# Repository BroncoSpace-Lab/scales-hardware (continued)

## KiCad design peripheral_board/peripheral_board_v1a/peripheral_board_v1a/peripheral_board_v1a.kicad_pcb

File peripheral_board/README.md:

# Peripheral Board
The peripheral board is conprized for two different purposes.

1. Inter communication between the Jetson and i.MX8X.
2. Gives the end user access to ports to attach the peripherals that they want. 
    The ports given to user:
    * At least 1 Ethernet port
    * At least 2 SPI/UART ports
## General Information of each major block of the board

The above image is of the root page of the schematic with basic infomration and a block diagram of the board and its use.

This is the front of the board in KiCad's 3D view.

Some of the models are not in the correct placement beacuse their 3D model was incorrectly created. They are placed in the correctly on the board.

This is the back of the board in KiCad's 3D view.

## Break down of the three core parts
Each section is about the individual chips and it has basic information on the layout.

### Raspberry Pi
[JLC Link](https://jlcpcb.com/partdetail/RaspberryPi-RP2350A/C42411118) to the RP2350A.

Layout and other information from the [PROVES dev kit](https://github.com/proveskit) and the [Raspberry Pi Hardware minimum configuration](extension://efaidnbmnnnibpcajpcglclefindmkaj/https://datasheets.raspberrypi.com/rp2350/hardware-design-with-rp2350.pdf)

This can be bought as a development board as a standalone product for project use.

### Wiznet
[JLC Link](https://jlcpcb.com/partdetail/Wiznet-W5500/C32843) to the Wiznet W5500.

Layout and other informatuon from the [PROVES dev kit](https://github.com/proveskit) and [Wiznet W5500 Eval Board](https://github.com/Wiznet/W5500-EVB)

This product can be purchased bought as [WIZ850io](https://wiznet.io/products/network-modules/wiz850io) which is a compact module of just the chip and an RJ45 or as [W5500-EVB-Pico](https://wiznet.io/products/evaluation-boards/w5500-evb-pico) which is the chip with a Raspberry Pi Pico with open holes for GPIO manipulation.

There is [Coding with CircuitPython on W5100S-EVB-Pico2](https://maker.wiznet.io/viktor/projects/coding-with-circuitpython-on-w5100s-evb-pico2/) that is on the Wiznet Makers website that should be easy to follow for setting up the Wiznet RP combination.

### 5-port Ethernet Switch
[JLC Link](https://jlcpcb.com/partdetail/MicrochipTech-KSZ8795CLXIC/C69416) to the Microchip 5-Port Ethernet Switch.

The original eval board is no longer made but there is an update of the chip with a [newer Eval Board](https://www.microchip.com/en-us/development-tool/KSZ8795CLXD-EVAL). For this project we will be using the strap in mode of the chip to be just a 4 port etherenet switch that will not require any software or modification. The last port will be left open for possible future iterations.

## How to used the board
*Still in Development*

*Taken with a grain of salt*
The Wizenet W5500 and Microchip KSZ8795CLXIC should be preconfigured to work as is. The Microchip KSZ8795CLXIC could be one reconfigured to utilize the 5th port as different data rates if they are needed.

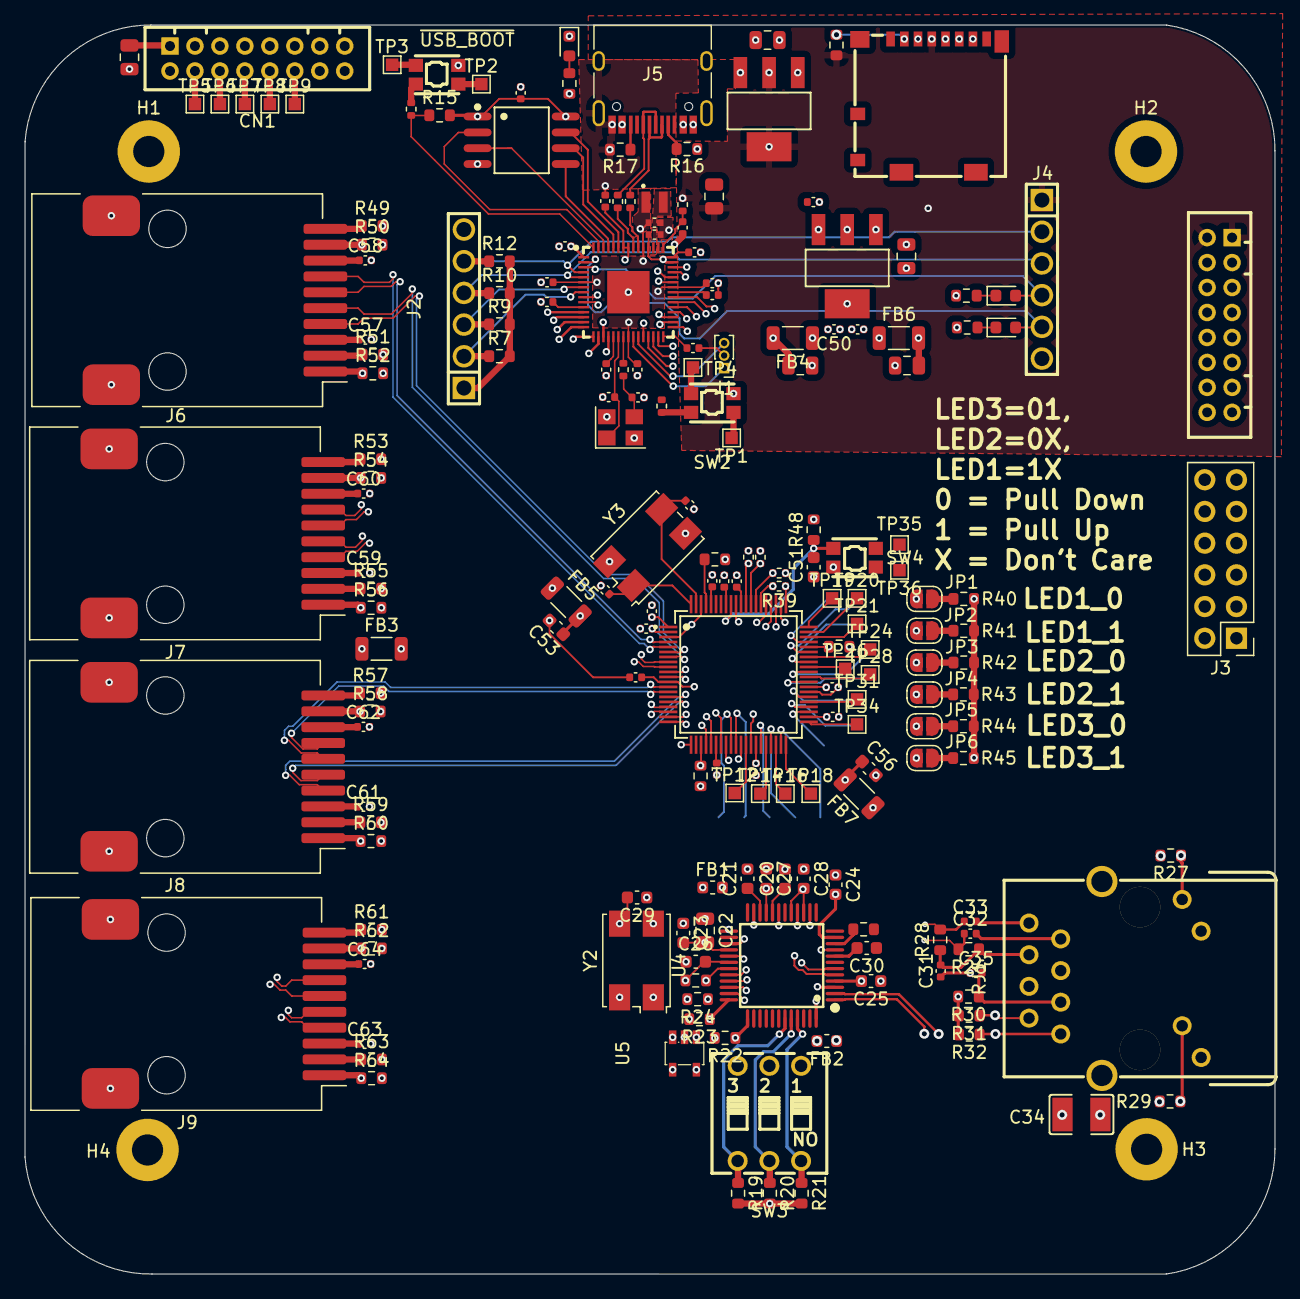
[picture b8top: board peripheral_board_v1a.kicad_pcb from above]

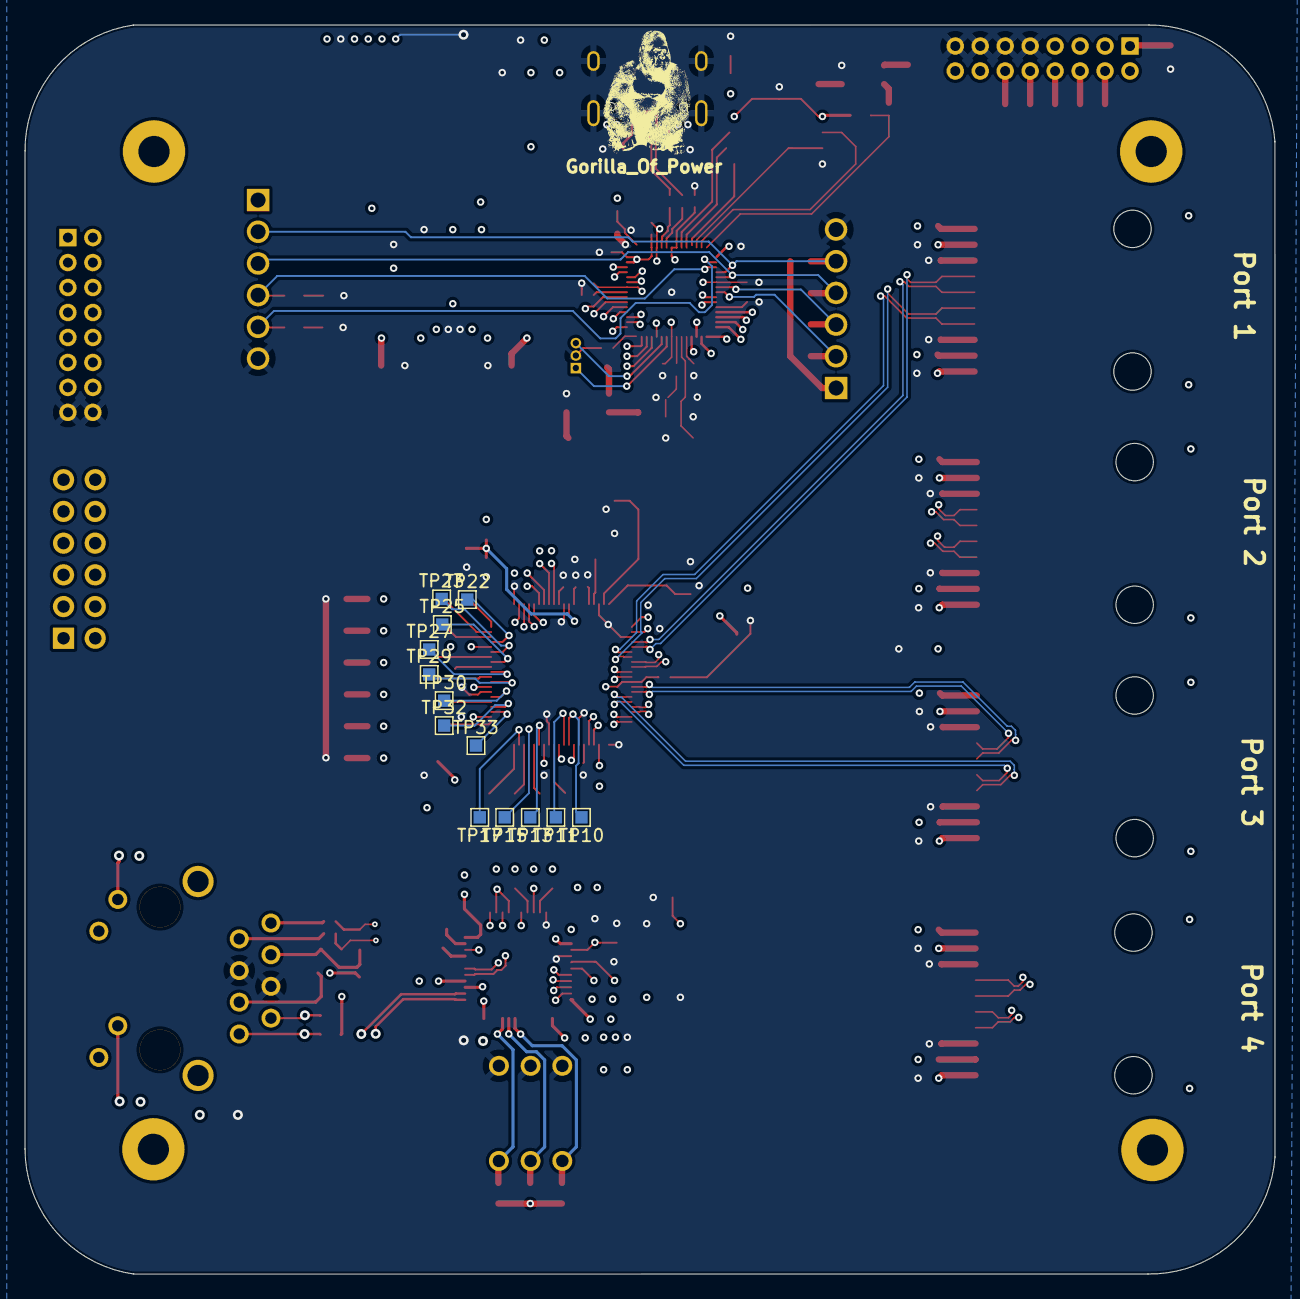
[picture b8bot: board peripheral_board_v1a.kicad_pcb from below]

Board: 6 copper layers, 100.2 x 100.1 mm, 211 parts (14 on the bottom side), 179 nets.

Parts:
C1, C2: 4.7uF; C_0402_1005Metric_small_pads
C3, C8, C9, C10, C11, C12, C13, C14, C15, C19, C36, C37, C38, C39, C40, C41, C42, C43, C44, C47, C48, C50, C52: 100nF; C_0402_1005Metric
C4, C5: 15pF; C_0402_1005Metric
C6, C7: 4.7uF; C_0402_1005Metric
C16, C18, C22: 10uF; C_0805_2012Metric
C17: 22uF; C_0805_2012Metric
C20, C30, C51: 10uF; C_0603_1608Metric
C21, C23, C24, C25, C27, C28: 0.1uF; C_0603_1608Metric
C26, C29: 18pF; C_0603_1608Metric
C31, C35: 10nF; C_0402_1005Metric
C32, C33: 6.8nF; C_0402_1005Metric
C34: 1nF/2kV; C1210
C45, C46: 18pF; C_0402_1005Metric
C49, C54, C55: 100uF; C_0805_2012Metric
C53, C56: 22uF; C_0603_1608Metric
C57, C58, C59, C60, C61, C62, C63, C64: 0.1uF; C_0402_1005Metric
CN1: Power Board Connector; CONN-TH_DF11-16DP-2DSA-08
CN2: DF11-16DP-2DSA(08); CONN-TH_DF11-16DP-2DSA-08
D1, D2, D3: LED; LED_0603_1608Metric
FB1, FB2: HH-1M1608-121JT; L_0603_1608Metric
FB3, FB4, FB5, FB6, FB7: FerriteBead; L_1206_3216Metric
Gorilla_Of_Power: LOGO
H1, H2, H3, H4: MountingHole; MountingHole_2.5mm_Pad
J1: Conn_01x03_Pin; PinHeader_1x03_P1.00mm_Vertical
J2, J4: Conn_01x06; HDR-TH_6P-P2.54-V-M-1
J3: Conn_02x06_Odd_Even; PinHeader_2x06_P2.54mm_Vertical
J5: USB_C_Receptacle_USB2.0_16P; USB_C_Receptacle_HRO_TYPE-C-31-M-12
J6, J7, J8, J9: RJ45_Pulse_JXD6-0001NL; RJ45_Pulse_JXD6-0001NL_Horizontal
JP1, JP2, JP3, JP4, JP5, JP6: SolderJumper_2_Open; SolderJumper-2_P1.3mm_Open_RoundedPad1.0x1.5mm
L1: 3.3uH; IND-SMD_L2.0-W1.6_AOTA-B201610S3R3-101-T
R1, R3, R4: 1k; R_0402_1005Metric
R2: 33; R_0402_1005Metric
R5, R6: 27; R_0402_1005Metric
R7, R8, R9, R10, R12, R14, R19, R20, R21, R48: 10k; R_0603_1608Metric
R11, R13, R49, R50, R51, R52, R53, R54, R55, R56, R57, R58, R59, R60, R61, R62, R63, R64: 1k; R_0603_1608Metric
R15: 0; R_0603_1608Metric
R16, R17: 5.1k; R_0603_1608Metric
R18, R35: 12.4k; R_0603_1608Metric
R22, R23, R24, R33, R34: 4.7k; R_0603_1608Metric
R25: 1M; R_0603_1608Metric
R26, R28, R31, R32: 49.9; R_0603_1608Metric
R27, R29: 330; R_0603_1608Metric
R30: 10; R_0603_1608Metric
R36, R38: 10k; R_0402_1005Metric
R37: 4.7k; R_0402_1005Metric
R39: 350; R_0402_1005Metric
R40, R41, R42, R43, R44, R45: 750; R_0603_1608Metric
RJ1: RB1-125BAG1A; RJ45-TH_RB1-125BAG1A
SIM1: 1040310811; SIM-SMD_8P-1040310811
SW1, SW2, SW4: EVPAA602W; KEY-TH_4P-L3.5-W4.9-P2.80-LS4.3
SW3: 3_Pin_Dip_Switch_DSWB03LHGET_C25503178; SW-TH_DSWB03LHGET
TP1, TP2, TP3, TP4, TP5, TP6, TP7, TP8, TP9, TP10, TP11, TP12, TP13, TP14, TP15, TP16, TP17, TP18, TP19, TP20, TP21, TP22, TP23, TP24, TP25, TP26, TP27, TP28, TP29, TP30, TP31, TP32, TP33, TP34, TP35, TP36: TestPoint; TestPoint_Pad_1.0x1.0mm
U1: RP2350A_C42411118; QFN-60_L7.0-W7.0-P0.40-TL-EP3.4
U2: AZ1117CH-3.3TRG1; SOT-223-3_L6.5-W3.4-P2.30-LS7.0-BR
U3: W25Q128JVSIQTR; SOIC-8_L5.3-W5.3-P1.27-LS8.0-BL
U4: W5500; LQFP-48_L7.0-W7.0-P0.50-LS9.0-BL
U5: SN74AHC1G125DBVR; SOT-23-5_L3.0-W1.7-P0.95-LS2.8-BR
U6: KSZ8795CLXIC; LQFP-80_L10.0-W10.0-P0.40-LS12.2-BL
U7: AZ1117CH-1.2TRG1; SOT-223-3_L6.5-W3.4-P2.30-LS7.0-BR
Y1: ABM8-272-T3; Crystal_SMD_3225-4Pin_3.2x2.5mm
Y2: 25MHz; Crystal_SMD_7050-4Pin_7.0x5.0mm
Y3: ABMM-25.000MHZ-B2-T; Crystal_SMD_7050-4Pin_7.0x5.0mm

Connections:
1.2A: C40.2, C54.2, FB4.2, U6.1 (VDD12A)
1.2D: C36.2, C42.2, C43.2, C55.2, FB6.2, U6.26 (VDD12D), U6.42 (VDD12D), U6.73 (VDD12D)
3V3A: C24.2, C25.2, C27.2, C28.2, C30.2, FB1.2, R30.2, R31.2, R32.2, U4.4 (AVDD), U4.8 (AVDD), U4.11 (AVDD), U4.15 (AVDD), U4.17 (AVDD), U4.21 (AVDD)
+1V1: C2.1, C3.1, C6.1, C8.1, L1.1, U1.6 (DVDD), U1.23 (DVDD), U1.39 (DVDD), U1.50 (VREG_FB)
+3V3: C1.1, C9.1, C10.1, C11.1, C12.1, C13.1, C14.1, C15.1, C17.2, C18.1, C19.1, C22.2, C23.2, CN1.1, CN1.3, CN1.5, CN1.7, CN2.1, CN2.2, FB1.1, FB5.1, FB7.1, J2.1, J3.1, J3.2, J4.1, R2.2, R7.2, R9.2, R10.2, R12.2, R14.2, R15.2, R19.2, R20.2, R21.2, R22.2, R23.2, R24.2, R27.2, R29.1, R49.2, R51.2, R53.2, R55.2, R57.2, R59.2, R61.2, R63.2, SIM1.4 (VDD), U1.1 (IOVDD), U1.11 (IOVDD), U1.20 (IOVDD), U1.30 (IOVDD), U1.38 (IOVDD), U1.44 (ADC_AVDD), U1.45 (IOVDD), U1.49 (VREG_VIN), U1.53 (USB_OTP_VDD), U1.54 (QSPI_IOVDD), U2.2 (Vout), U2.4 (Vout), U3.1 (~CS), U3.8 (VCC), U4.28 (VDD), U5.5 (VCC)
/Raspberry_pi/ QSPI_SS: R1.1, R15.1, U1.60 (QSPI_SS)
/Raspberry_pi/QSPI_DATA_0: U1.57 (QSPI_SD0), U3.5 (DI)
/Raspberry_pi/QSPI_DATA_1: U1.59 (QSPI_SD1), U3.2 (DO)
/Raspberry_pi/QSPI_DATA_2: U1.58 (QSPI_SD2), U3.3 (IO2)
/Raspberry_pi/QSPI_DATA_3: U1.55 (QSPI_SD3), U3.7 (IO3)
/Raspberry_pi/QSPI_SCK: U1.56 (QSPI_SCLK), U3.6 (CLK)
/Raspberry_pi/~USB_BOOT: R1.2, SW1.1'
CGND: C34.1, RJ1.13 (GND), RJ1.14 (GND)
Chassis_GND: FB3.1, J6.SH, J7.SH, J8.SH, J9.SH
D+: J5.A6 (D+), J5.B6 (D+), R5.1
D-: J5.A7 (D-), J5.B7 (D-), R6.1
GND: C1.2, C2.2, C3.2, C4.1, C5.1, C6.2, C7.2, C8.2, C9.2, C10.2, C11.2, C12.2, C13.2, C14.2, C15.2, C16.1, C17.1, C18.2, C19.2, C22.1, C23.1, C26.1, C29.1, C34.2, C36.1, C37.1, C38.1, C39.1, C40.1, C41.1, C42.1, C43.1, C44.1, C45.2, C46.2, C47.1, C48.1, C49.1, C50.1, C51.2, C52.1, C53.2, C54.1, C55.1, C56.2, C57.2, C58.2, C59.2, C60.2, C61.2, C62.2, C63.2, C64.2, CN1.9, CN1.11, CN1.13, CN1.15, CN2.15, CN2.16, D1.1 (K), FB2.1, FB3.2, J1.2, J2.6, J4.6, J5.A1 (GND), J5.A12 (GND), J5.B1 (GND), J5.B12 (GND), J5.S1 (SHIELD), R11.2, R13.2, R16.1, R17.1, R35.2, R39.1, R40.2, R41.2, R42.2, R43.2, R44.2, R45.2, R50.2, R52.2, R54.2, R56.2, R58.2, R60.2, R62.2, R64.2, RJ1.4, RJ1.5, SIM1.6 (VSS), SW1.2, SW2.2, SW3.4, SW3.5, SW3.6, SW4.2, U1.47 (VREG_PGND), U1.61 (GND), U2.1 (ADJ/GND), U3.4 (GND), U4.23 (RSVD), U4.29 (GND), U5.3 (GND), U6.3 (GNDA), U6.21 (GNDA), U6.27 (GNDD), U6.33 (GNDD), U6.47 (GNDD), U6.61 (GNDD), U6.71 (GNDD), U6.78 (GNDA), U7.1 (GND), Y1.2, Y1.4, Y2.2, Y2.4, Y3.2, Y3.4
GNDA: C20.2, C21.2, C24.1, C25.1, C27.1, C28.1, C30.1, C31.1, C35.1, FB2.2, R18.1, U4.3 (AGND), U4.9 (AGND), U4.14 (AGND), U4.16 (AGND), U4.19 (AGND), U4.48 (AGND)
GPIO14: CN1.14, U1.18 (GPIO14)
GPIO15: CN1.16, U1.19 (GPIO15)
GPIO22: J3.3, U1.34 (GPIO22)
GPIO23: J3.5, U1.35 (GPIO23)
GPIO24: J3.7, U1.36 (GPIO24)
GPIO25: J3.9, U1.37 (GPIO25)
GPIO26_ADC0: J3.4, U1.40 (GPIO26_ADC0)
GPIO27_ADC1: J3.6, U1.41 (GPIO27_ADC1)
GPIO28_ADC2: J3.8, U1.42 (GPIO28_ADC2)
GPIO29_ADC3: J3.10, U1.43 (GPIO29_ADC3)
GREEN_LED: RJ1.10 (LLED-), U4.25 (LINKLED)
I2C0_SCL: J2.2, R7.1, U1.8 (GPIO5)
I2C0_SDA: J2.3, R9.1, U1.7 (GPIO4)
I2C1_SCL: J2.4, J4.3, R10.1, U1.5 (GPIO3)
I2C1_SDA: J2.5, J4.2, R12.1, U1.4 (GPIO2)
INTR_N: R33.2, U6.23 (INTR_N)
INTn: R23.1, U1.33 (GPIO21), U4.36 (INTn)
LED1_0: J6.1, JP1.1 (A), R52.1, U6.65 (LED10)
LED1_1: J6.9, JP2.1 (A), R50.1, U6.64 (LED11)
LED2_0: J7.1, JP3.1 (A), R56.1, U6.63 (LED20)
LED2_1: J7.9, JP4.1 (A), R54.1, U6.62 (LED21)
LED3_0: J8.1, JP5.1 (A), R60.1, U6.25 (LED3_0)
LED3_1: J8.9, JP6.1 (A), R58.1, U6.24 (LED3_1)
LED4_0: J9.1, R64.1, U6.31 (LED4_0)
LED4_1: J9.9, R62.1, U6.28 (LED4_1)
unnamed: C5.2, R4.1, Y1.3
unnamed: C32.2, RJ1.7
unnamed: C33.2, RJ1.8
unnamed: C49.2, C50.2, C52.2, FB4.1, FB6.1, U7.2 (VOUT), U7.4 (VOUT)
unnamed: CN1.4, TP5.1
unnamed: CN1.6, TP6.1
unnamed: CN1.8, TP7.1
unnamed: CN1.10, TP8.1
unnamed: CN1.12, TP9.1
unnamed: D1.2 (A), R8.1
unnamed: D2.1 (K), R11.1
unnamed: D3.1 (K), R13.1
unnamed: J3.11, J3.12
unnamed: J5.A5 (CC1), R16.2
unnamed: J5.B5 (CC2), R17.2
unnamed: J6.2, R51.1
unnamed: J6.10, R49.1
unnamed: J7.2, R55.1
unnamed: J7.10, R53.1
unnamed: J8.2, R59.1
unnamed: J8.10, R57.1
unnamed: J9.2, R63.1
unnamed: J9.10, R61.1
unnamed: JP1.2 (B), R40.1
unnamed: JP2.2 (B), R41.1
unnamed: JP3.2 (B), R42.1
unnamed: JP4.2 (B), R43.1
unnamed: JP5.2 (B), R44.1
unnamed: JP6.2 (B), R45.1
unnamed: R3.2, SW2.1'
unnamed: R29.2, RJ1.9 (LLED+)
unnamed: R27.1, RJ1.11 (RLED+)
unnamed: SW1.1, TP2.1
unnamed: SW1.2', TP3.1
unnamed: SW2.1, TP1.1
unnamed: SW2.2', TP4.1
unnamed: SW4.1', TP35.1
unnamed: SW4.2', TP36.1
unnamed: R3.1, U1.26 (RUN)
unnamed: R6.2, U1.51 (USB_DM)
unnamed: R5.2, U1.52 (USB_DP)
unnamed: C7.1, R2.1, U1.46 (VREG_AVDD)
unnamed: L1.2, U1.48 (VREG_LX)
unnamed: C4.2, U1.21 (XIN), Y1.1
unnamed: R4.2, U1.22 (XOUT)
unnamed: C21.1, U4.22 (1V2O)
unnamed: R18.2, U4.10 (EXRES1)
unnamed: C20.1, U4.20 (TOCAP)
unnamed: C26.2, R25.1, U4.30 (XI/CLKIN), Y2.1
unnamed: C29.2, R25.2, U4.31 (XO), Y2.3
unnamed: TP24.1, U6.54 (COL5)
unnamed: TP25.1, U6.53 (CRS5)
unnamed: R35.1, U6.77 (ISET)
unnamed: TP23.1, U6.55 (REFCLKO)
unnamed: TP32.1, U6.44 (RXC5/GRXC5)
unnamed: TP31.1, U6.45 (RXD5_0)
unnamed: TP30.1, U6.46 (RXD5_1)
unnamed: TP29.1, U6.49 (RXD5_2)
unnamed: TP28.1, U6.50 (RXD5_3)
unnamed: TP22.1, U6.57 (RXD5_4)
unnamed: TP21.1, U6.58 (RXD5_5)
unnamed: TP20.1, U6.59 (RXD5_6)
unnamed: TP19.1, U6.60 (RXD5_7)
unnamed: TP27.1, U6.51 (RXDV5/CRSDV5/RXD5_CTL)
unnamed: TP26.1, U6.52 (RXER5)
unnamed: TP33.1, U6.43 (TXC5/REFCLKI5/GTXC5)
unnamed: TP11.1, U6.30 (TXD5_0)
unnamed: TP12.1, U6.32 (TXD5_1)
unnamed: TP13.1, U6.35 (TXD5_2)
unnamed: TP14.1, U6.36 (TXD5_3)
unnamed: TP16.1, U6.38 (TXD5_4)
unnamed: TP17.1, U6.39 (TXD5_5)
unnamed: TP18.1, U6.40 (TXD5_6)
unnamed: TP34.1, U6.41 (TXD5_7)
unnamed: TP10.1, U6.29 (TXEN5/TXDS5_CTL)
unnamed: TP15.1, U6.37 (TXER5)
unnamed: C46.1, U6.79 (XI), Y3.3
unnamed: C45.1, U6.80 (XO), Y3.1
PME_N: R34.2, U6.56 (PME)
PMODE0: R21.1, SW3.1, U4.45 (PMODE0)
PMODE1: R20.1, SW3.2, U4.44 (PMODE1)
PMODE2: R19.1, SW3.3, U4.43 (PMODE2)
R1CT: C58.1, J6.8 (RCT)
R2CT: C60.1, J7.8 (RCT)
R3CT: C62.1, J8.8 (RCT)
R4CT: C64.1, J9.8 (RCT)
RCT: C31.2, R26.1, R28.1, RJ1.6
RST_N: C51.1, R48.2, SW4.1, U6.72 (RST_N)
RSTn: R22.1, U1.32 (GPIO20), U4.37 (RSTn)
RX: D2.2 (A), J4.4, U1.3 (GPIO1)
RX1+: J6.6 (RD+), U6.4 (RXP1)
RX1-: J6.7 (RD-), U6.5 (RXM1)
RX2+: J7.6 (RD+), U6.8 (RXP2)
RX2-: J7.7 (RD-), U6.9 (RXM2)
RX3+: J8.6 (RD+), U6.13 (RXP3)
RX3-: J8.7 (RD-), U6.14 (RXM3)
RX4+: J9.6 (RD+), U6.17 (RXP4)
RX4-: J9.7 (RD-), U6.18 (RXM4)
RX +: C32.1, R26.2, U4.6 (RXP)
RX -: C33.1, R28.2, U4.5 (RXN)
SPI0_CS1: R24.1, U4.32 (SCSn)
SPI0_CSO: R14.1, SIM1.2 (CD/DAT3), U1.28 (GPIO17)
SPI0_ETHER: U4.34 (MISO), U5.2 (A)
SPI0_MISO: SIM1.7 (DAT0), U1.27 (GPIO16), U5.4 (Y)
SPI0_MOSI: SIM1.3 (CMD), U1.31 (GPIO19), U4.35 (MOSI)
SPI0_SCK: SIM1.5 (CLK), U1.29 (GPIO18), U4.33 (SCLK), U5.1 (~OE)
SPI1_CS1: CN2.12, R36.1, U1.17 (GPIO13), U6.69 (SPIS_N)
SPI1_RX: CN2.8, R37.1, U1.16 (GPIO12), U6.68 (SDA_MDIO)
SPI1_SCK: CN2.10, R38.1, U1.14 (GPIO10), U6.67 (SCL_MDC)
SPI1_TX: CN2.14, R39.2, U1.15 (GPIO11), U6.66 (SPIQ)
SWCLK: J1.1, U1.24 (SWCLK)
SWD: J1.3, U1.25 (SWD)
T1CT: C57.1, J6.3 (TCT)
T2CT: C59.1, J7.3 (TCT)
T3CT: C61.1, J8.3 (TCT)
T4CT: C63.1, J9.3 (TCT)
TCT: C35.2, R30.1, RJ1.3
TX: D3.2 (A), J4.5, U1.2 (GPIO0)
TX1+: J6.4 (TD+), U6.6 (TXP1)
TX1-: J6.5 (TD-), U6.7 (TXM1)
TX2+: J7.4 (TD+), U6.10 (TXP2)
TX2-: J7.5 (TD-), U6.11 (TXM2)
TX3+: J8.4 (TD+), U6.15 (TXP3)
TX3-: J8.5 (TD-), U6.16 (TXM3)
TX4+: J9.4 (TD+), U6.19 (TXP4)
TX4-: J9.5 (TD-), U6.20 (TXM4)
TX +: R32.1, RJ1.1, U4.2 (TXP)
TX -: R31.1, RJ1.2, U4.1 (TXN)
UART1_CTS: CN2.7, U1.9 (GPIO6)
UART1_RTS: CN2.9, U1.10 (GPIO7)
UART1_RX: CN2.5, U1.13 (GPIO9)
UART1_TX: CN2.3, U1.12 (GPIO8)
VBUS: C16.2, C48.2, J5.A4 (VBUS), J5.A9 (VBUS), J5.B4 (VBUS), J5.B9 (VBUS), R8.2, U2.3 (Vin), U7.3 (INPUT)
VDDAT: C38.2, C39.2, C41.2, C53.1, FB5.2, U6.2 (VDDAT33), U6.12 (VDDAT33), U6.76 (VDDAT33)
VDDIO: C37.2, C44.2, C47.2, C56.1, FB7.2, R33.1, R34.1, R36.2, R37.2, R38.2, R48.1, U6.34 (VDDIO), U6.48 (VDDIO), U6.70 (VDDIO)
YELLOW_LED: RJ1.12 (RLED-), U4.27 (ACTLED)

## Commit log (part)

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2025-04-04 WD Default config changed
    Pulled up WD OBC, and pulled down Jetson and Perif. WD
2025-04-04 Test
2025-04-07 Small Revisions
2025-04-10 prep docs and current schematic pdf for hardware review
2025-04-11 Moved Power System folder to root
2025-04-14 Deleted Duplicates
2025-04-15 Clean up of RJ45
2025-04-17 Update to PCB
    Made added the rest of the Wiznet chip. Unsure how to put the test pads on the underside of the board.
2025-04-21 Some oopsies but fixed Them, routed one segment
2025-04-23 Minor changes to schematic
2025-04-29 Updated the PCB and the Schematic
    Added in the strap in mode. Almost done with the RP schematic and the will then have to route signals.
2025-05-01 Added picture to create a block diagram
    Placed pictures and wires with some text to give a block diagram.
    Looked through the data sheets and found some info on the power for the ethernet switch. The power needs to go through a ferrite bead. Since we are getting power through a USB port I will use voltage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
    Tried to get the same version that we are using for the raspberry pi pico but the easyeda2kicad was not working. There is already one that was from the dev board that I have placed but I would like t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
2025-05-01 Revisions to Schematic
    Added request to add I2C buffer
    Added request to modify block diagram to figure out WD con ops
    Added pull up to OBC WD for proper SHDN use.
2025-05-06 Schematic Revisions
    Added updated block diagram
    Added Individual watch dog setups for each subsystem. Resistor and Capacitor values must be modified to reflect desired time range.
2025-05-07 Layout Complete
    Added I2C buffer
    Found replacement inductor for 10uH
    Added footprints for new components
    Last thing missing is changing the solder mask sizing on most footprints to remove the errors.
2025-05-08 Update to PCB and minor changes to schematic
    Completed the RP2350 layout. Put in the edge cut that should match the IMX flight board.
    Had to rewire the Ethernet ports but finished one just need to copy and paste it to the others. Once that is done and connected to the Wiznet I can move to the switch.
2025-05-13 Update to schematic and worked on PCB
    Made a few changes with signals for the ethernet switch schematic. Made it easier for the traces for power.
    Put all the decoupling capacitors onto the ethernet switch chip on the PCB. Was able to route the traces for the Wiznet. Might want to change where the signals are. Want to look into maybe making the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
    Just need to connect the power of 1.2 volts that the ethernet switch needs and then will be able to route the 4 other ethernet switches. I am being sure to use the pair routing for the length.
    Side note figured out how to add images as a layer, which is fun!
2025-05-19 Updated Shematic
    Added Conn. Ops
2025-05-21 Cleaned up Board
    Removed DRC errors due to constraint inconsistencies with pre-defined via and track sizes.
    Removed Annular Ring error from the DRC, had to allow for 0mm ring size, this is due to the RJ45 footprints.
2025-05-22 Fixed Ugly Trace
2025-05-26 EPS Changes
    Updated Mounting hole size from 2.6mm to 2.5mm
2025-05-27 Little Changes before Changing Everything again
2025-05-28 Update to schematic and readme
    Made the schematic root page have more info and be a better block diagram.
    Updated the readme with some more general info on the board and what it is based on.
2025-05-29 Fixed this POS, it accidentally removed my stuff
2025-05-29 minor changes
2025-05-29 Revert "Updated .sch names"
    This reverts commit 74cd391a8fa3c918ce36f01b2b9573e3d642e9f0.
2025-05-30 More Goodies
    Updated Inductor footprints with most readily available LCSC counterparts
    Updated XT-60 connector
    Updated Edge-Cuts board size
    Updated Diode Footprints to fix DRC errors
    Started Board layout and copper fills for power and ground
2025-05-31 Updates for JLC
2025-06-03 Cleaned up Layout
    Fixed to work with JLC recommendations. Prepping for review with Andrew
2025-06-03 Fixes of part selection for the board and generating the files
2025-06-03 Revert "Revert "prep to transfer to docs repo""
    This reverts commit a3a901247cace750a207385ef1c305f9f14b8320.
    modified: docs/imx8x_procedures.md
    new file: docs/imx_yocto_bsp.md
    new file: docs/power_system.md
    new file: docs/scales_demo.md
    modified: mkdocs.yml
2025-06-04 Production Files Generated for RevD
    Beating a dead horse at this point. Should be done
2025-06-05 Signal1 Fill and Signal2 Fills Added
    Fixed DFM Error in manufacturing process due to lack of fills to seperate tracks.
2025-06-10 Minor changes for the board
    Added some references and notes to the board.
    Notes on things that we should maybe remove them.
    Added a simple version of SPI and QSPI.
2025-06-10 Updated Symbol Library Locations
2025-06-11 Schematic Updates
    WIP
2025-06-11 Fixed Image implementation
    House keeping stuff
2025-06-13 SOM signal finished
    Finished labeling the SOM. Handing the board off to Luca to go and configure the rest of the board and look over the rest of the schematic.
    Need to finish the SOM with pull up/down or ground any unused signals.
2025-06-17 WIP
    Removed pull up resistor to I2C buffer. Fixed R66 in OBC Subsystem causing 10v output instead of 3.3v
2025-06-18 housekeeping WIP
2025-06-18 REV E / Viking 1-B Complete
    Shrunk down many component sizes
    Fixed ST pin with pull down LED to a (hopefully functional one)
    Fixed Inductor values from incorrect calculations
    Fixed incorrect resistor values for OBC subsystem
    Redid layout and routing
    Watch dog routing has been redone
2025-06-19 Fixed Small Layout Problem with VD
    Didnt want to redo layout so instead I added a resistor to drop some voltage
2025-06-20 Minor KiCad Changes
    Combing through my KiCad Design and making sure that everything is up to standard.
    Board seems to be a bit off and doesn't seem to to be working correctly.
    There are a couple things to note.
    For the Wiznet there are different configurations that seem to me that were unclear and require a closer look.
    For the Ethernet Switch I need to make sure it is being power correctly and I might need to had in the other ethernet switch to ensure that it works as intended because the 5th port I left open but t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
2025-06-20 Put Decoupling Caps next to SOM connector
2025-06-24 Update to the PCB
    #Changes made so far
    ## Wiznet
    * Changed the Wiznet layout to match that of their development board
    * Restructured the RJ45 connections
    * *Looked over the RJ45 still a unsure*
    * Added in 2 differnt versions of Ethernt Connections. The one that shows the magnetics might be used for the Ethernet switch.
2025-06-24 Updated Gecko Variant
    Fixed missing 3d model.
2025-06-25 Board Layout WIP
2025-06-26 Still Routing. :/ WIP
2025-06-28 PCB layout
    Added a new version of the board that went from 4 layers to 6.
    Started the 6 layer board and moving forward with it.
    Need to restructure the board and use the via in pads.
    The wiznet is basically done just needs to be placed on the board.
    The RP is almost done but the GPIO is broken out but still need to put in the pins.
    Ethernet switch is mostly done. Need to figure out routing for the test pads and then place the RJ45 ports on the board. Once I have the ports and the chip in place there calculations have already be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
2025-07-01 added the funny
2025-07-02 PCB should be done
    Finished the PCB just needs a review and then the part selection should be easy.
    Added in stitching Vias.
    Added in a Power controller for the two power sources of the USB or the external power board.
    Removed the microSD card reader and added in XTSD which is just onboard NAND. It is around 1 gigabyte which should be enough space for any and all programs we are running.
2025-07-09 Part picking for board
2025-07-10 RevF Gecko Variant Added
    Added RevF Gecko Variant
2025-07-11 Done?
2025-07-15 Changes to the structure of the Folder
    Made more changes to the structure of the folder. Mainly just some renaming of the images and making sure the Readme is correct
2025-08-06 Layout Changes
    Consolidated the BOM a little bit, have to rerout
2025-08-06 Finished Routing.
    Completed routing and zone fills. Fixed some parts of the schematic as well.
2025-08-06 Generated Step
2025-08-10 stuff
2025-08-11 Refining Schematic Connections.
2025-08-26 Added Sub-sheet Descriptions
2025-08-28 Gerbers Generated
2025-09-02 Updated readme.md and Adapter board
2025-09-05 Switch Schematic Update
    The switch schematic should be done. Waiting on a review but should be ready for moving forward with board layout.
2025-09-11 Board layout WIP
    Redid the placement of the board due to the structure which should be good now. Started to put stuff on the back of the board to make sure that there is enough space for the Ethernet signals. Have no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
2025-09-18 Ready to order the board
2025-09-26 Renamed something and reverted v2 to original production version
2025-10-15 Small changes from Microchip
2025-10-24 Did stufffffff
2025-10-24 good stufff
2025-10-29 Schematic Complete. Ready for Phytec.
    Fixed muxing with a few things that were missing with ETH1, and corrected some missing labels. Ready for Phytecs review.
2025-10-31 Changes to the board layout
    Need to finish doing some layout but waiting on Microchip to confirm with what I have. Might want to change the EDA symbol for the switch IC.
2025-11-07 Little changes to the PCB
    Made a little bit of some changes of the traces for the decoupling caps.
2025-12-02 Little Updates from Microchip
    Got some feedback from microchip right before the Holiday weekend and implemented them on to the board and asked some clarifying questions on what steps to do moving forward with some design guidelin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
2025-12-19 Forgot to save
    Forgot to save some of the changes of the signals before the last push.
2026-01-12 Added text to SPI breakout
2026-03-10 Started Cadence Sim of EPS
2026-03-14 Working on Simulation Models
    Got the TPS1 working. Got the LT8612 working. Working on the Comparator network for the watchdog
2026-03-17 added jetson
2026-03-17 Included all three models in full_eps.sim
    Needs to be run on a beefier machine, need to test rise times for subsystems.
2026-03-21 Differential pair routing complete for Ethernet PHY and MAC
2026-03-22 Board is complete. Time for review
2026-03-22 added pdf for pragun
2026-03-24 Small Fixes. Gerber Push
2026-03-25 Fixed USB problem. New STEP and GERBERS generated
2026-04-02 Reapply "Delete ~imx8x_eps_leviathan.kicad_sch.lck"
    This reverts commit 8216c13ce7caa1f9886631e12e95ca67fb38b01d.
2026-04-10 Created step file
2026-04-22 added R_Prot for CHA_GND
2026-04-23 Continued Layout
2026-04-23 Added some notes for phytec. Fixed CMD and SCK uSD card pull up.
2026-04-24 Did stuuuuuff
2026-04-25 added board outline
2026-05-18 Fixed an ERC error, and updated reference designators so there are no more conflicts
